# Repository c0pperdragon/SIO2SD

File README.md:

# SIO2SD
An Arduino-based floppy drive emulator for the Atari 8 bit computers.

This small Arduino build emulates an Atari 1050 floppy drive to connect
to an original Atari 8-bit computer. The program is compatible with
most Arduino boards. And for boards based on the Atmega32u4 it also provides
various log messages on the serial monitor to help debugging (mainly for my own use).

For a breadboard setup like my development device, you will need two push buttons,
two 7-digit LEDs and one SDCard socket (with built-in or separate level shifters) and
some wires and resistors. The connectivity is pretty standard and you will find
the details as comments in the source code.

For a more polished product, I have designed a PCB that can fit into a 3D-printed
case that resembles a tiny floppy drive with the SD card acting as a tiny floppy disk.

## Emulated floppies on SDcard
The floppy drive emulator needs an SDcard containing .ats files for each individual floppy disk.
Because there is no elaborated user-interface on the device, the naming and location of the files
need to follow a fixed system: The files are searched for in a directory ATARI/
on the root of the SDcard. Every disk file must be named nn_Anything.ats with two leading digits that correspond to the
numeric display on the device and the mandatory '_' character. Alternatively you can also
have a folder named nn_Anything with individual files inside. Such a folder will be emulated
as an read-only enhanced density floppy containing these files.

Currently only a very basic support for single density (720 sectors)
and enhanced density (1040 sectors) floppies is provided without special functions for any third-party devices.

## User interface
You can switch though the numbered disks 00 to 99 with the two buttons. This is the maximum number of disks 
supported on a single SDcard. When you switch beyond 99, you will see -- on the display, which means the device
now emulates a switched off floppy drive. Selecting a number for which no diskfile exists will simulate 
a device with no floppy inserted (in this case you can create a diskfile with the DOS format functions).

You can also emulate a second floppy drive, which is very usable for example for holding the save disks
for games that support this. To do so, you need to press both buttons to make the small indicator dot appear
on the left LCD block. This means that the number you see in the display is the floppy that is inserted
in drive 2. This floppy can now also be changed with the two buttons. It is even possible to select the same 
floppy in both drives at once (but this is probably of no great use).

## Latest hardware

## 3D-printed case

My brother went to greate lengths, designing a proper case for the floppy emulator. 
In my oppinion, this now looks absolutely phantastic.

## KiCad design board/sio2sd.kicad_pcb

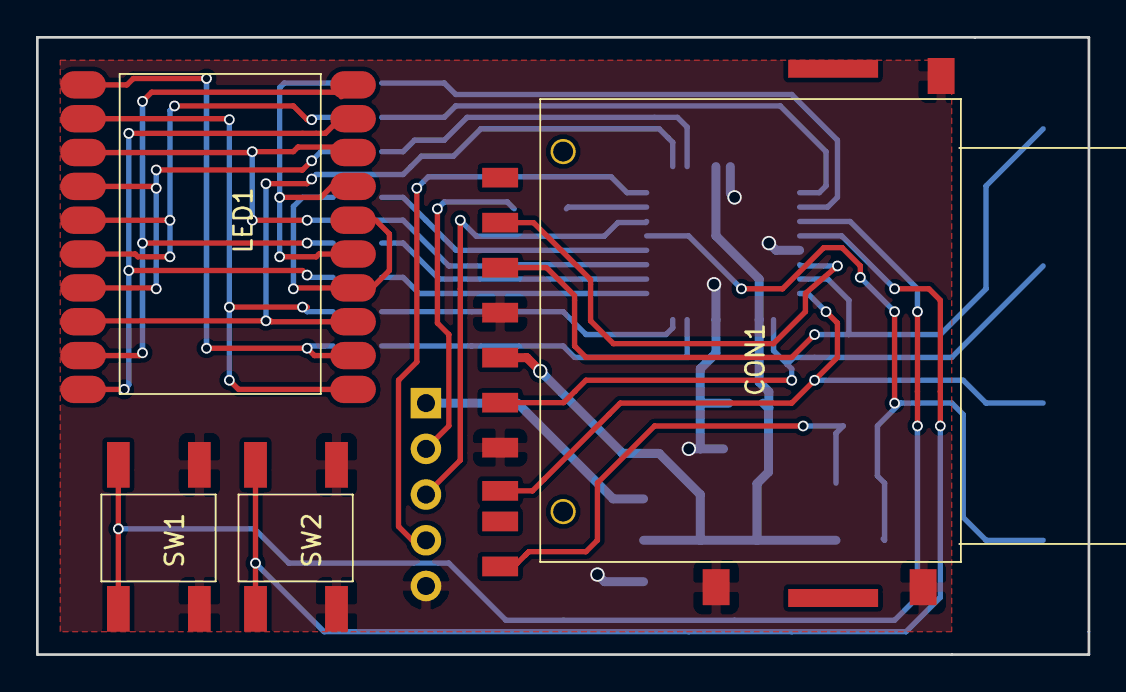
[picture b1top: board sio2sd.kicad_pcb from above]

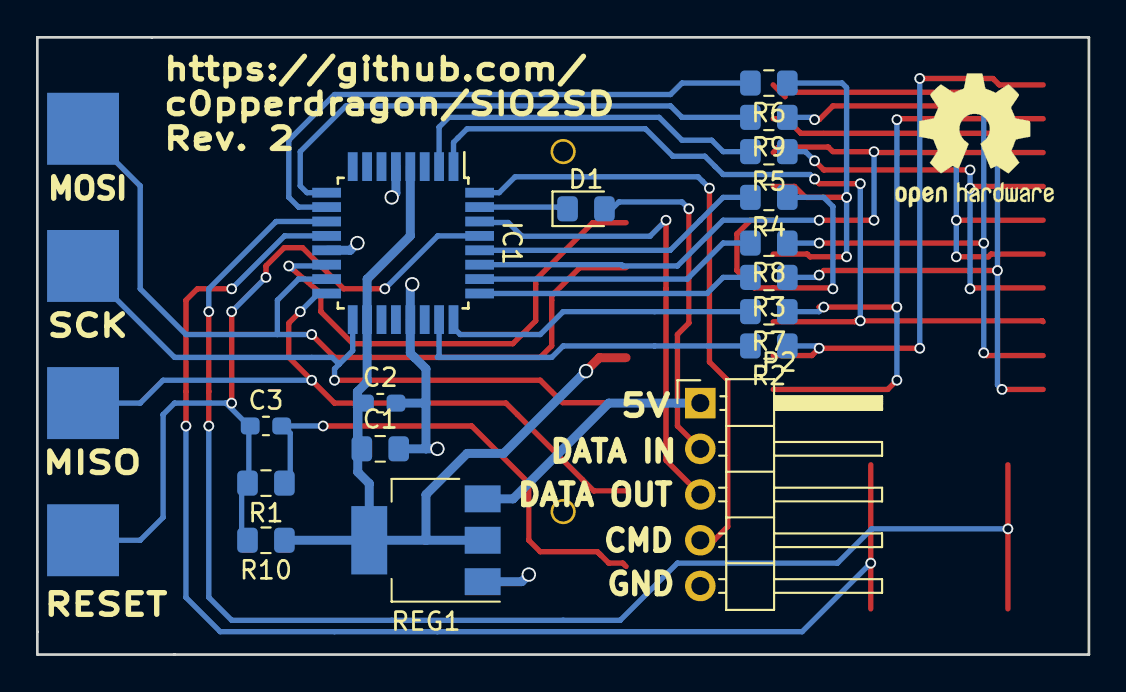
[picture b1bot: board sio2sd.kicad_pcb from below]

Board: 2 copper layers, 58.4 x 34.3 mm, 25 parts (21 on the bottom side), 33 nets.

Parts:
C1: 10uF; C_0805_2012Metric_Pad1.15x1.40mm_HandSolder
C2, C3: 100nF; C_0603_1608Metric_Pad1.05x0.95mm_HandSolder
CON1: SD_Card; sdcardsocket
D1: 0.2V; D_0805_2012Metric_Pad1.15x1.40mm_HandSolder
IC1: ATMEGA328PB-A; TQFP-32_7x7mm_P0.8mm
LED1: LED2DIGIT; led2digit
P2: SIO; PinHeader_1x05_P2.54mm_Horizontal
R1: 220k; R_0805_2012Metric_Pad1.15x1.40mm_HandSolder
R2, R3, R4, R5, R6, R7, R8, R9: 1k; R_0805_2012Metric_Pad1.15x1.40mm_HandSolder
R10: 10k; R_0805_2012Metric_Pad1.15x1.40mm_HandSolder
REG1: LM1117IMPX-3.3; SOT-223
SW1: UP; button
SW2: DOWN; button
W1: MOSI; pad
W2: MISO; pad
W3: SCK; pad
W4: Reset; pad

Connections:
+3V3: C1.1, C2.1, CON1.4, IC1.4, IC1.18, R10.1, REG1.2, REG1.4
+5V: P2.1, REG1.3
/CMD: IC1.32, P2.4
/ChipSelectSD: CON1.1, IC1.14
/Digit0: IC1.27, LED1.8, LED1.13
/Digit1: IC1.1, LED1.3, LED1.18
/MISO: CON1.7, IC1.16, W2.1
/MOSI: CON1.2, IC1.15, W1.1
/RX: IC1.30, P2.3
/Reset: C3.1, IC1.29, R1.2, R10.2, W4.1
/SCK: CON1.5, IC1.17, W3.1
/Seg_4: LED1.14, LED1.17, R5.1
/Seg_5: LED1.15, LED1.16, R9.1
/Seg_6: LED1.5, LED1.7, R6.1
/Seg_A0: LED1.2, LED1.11, R2.1
/Seg_A1: LED1.1, LED1.12, R7.1
/Seg_A2: LED1.9, LED1.20, R3.1
/Seg_A3: LED1.10, LED1.19, R8.1
/Seg_A5: LED1.4, LED1.6, R4.1
/TX: D1.2, P2.2
GND: C1.2, C2.2, CON1.3, CON1.6, CON1.11, CON1.12, CON1.13, IC1.5, IC1.13, IC1.21, P2.5, REG1.1, SW1.2, SW2.2
unnamed: C3.2, CON1.10, R1.1
unnamed: D1.1, IC1.31
unnamed: IC1.2, R5.2
unnamed: IC1.9, R9.2
unnamed: IC1.10, R6.2
unnamed: IC1.11, SW1.1
unnamed: IC1.12, SW2.1
unnamed: IC1.23, R2.2
unnamed: IC1.24, R7.2
unnamed: IC1.25, R3.2
unnamed: IC1.26, R8.2
unnamed: IC1.28, R4.2

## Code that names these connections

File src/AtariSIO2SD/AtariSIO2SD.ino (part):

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// -- connection to Atari SIO port
                              // default arduino RX -> serial data from Atari SIO pin 5
                              // default arduino TX -> serial data to Atari SIO pin 3
#define PIN_SIOCOMMAND  2     //                    -> CMD signal from Atari SIO pin 7

// -- connection to SDCARD
                              // default MOSI
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#define PIN_CHIPSELECT  10    // enables SDCARD on SPI bus

// -- connection to LED display and mode selector
#define PIN_DIGIT0 A4         // enables LED digit 0 (right digit)
#define PIN_DIGIT1 3          // enables LED digit 1 (left digit)
// the digit segments are differently assigned for digit 0 and 1  
//           segment:    a   b   c   d   e   f   g   DP
byte pin_segments0[8] = {A1, A0, A2, 6,  A5, 4,  5,  A3}; 
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    inputlock = false;
  
    // configure and turn of digit selectors 
    pinMode(PIN_DIGIT0, OUTPUT);
    digitalWrite (PIN_DIGIT0, LOW);
    pinMode(PIN_DIGIT1, OUTPUT);
    digitalWrite (PIN_DIGIT1, LOW);  
    // configure and turn off individual digits
    for (i=0; i<8; i++)
    {   pinMode(pin_segments0[i], OUTPUT);
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    if (activedigit==0) 
    {   byte value = selecteddisk[showndiskdrive];
        value = showerror ? 12 : ((value<=99) ? (value % 10) : 10);   // when drive is off: - 
        digitalWrite (PIN_DIGIT1, commoncathode ? HIGH : LOW);  // turn off digit 1
        byte i;
        byte v = digitpatterns[value];
        for (i=0; i<7; i++) 
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        if (activitylight[0]>0) { dot = !dot; }
        if (dot) { digitalWrite (pin_segments0[7], commoncathode ? HIGH : LOW); }
        else     { digitalWrite (pin_segments0[7], commoncathode ? LOW : HIGH); }
        digitalWrite (PIN_DIGIT0, commoncathode ? LOW : HIGH);  // turn on digit 0
    }
    else 
    {   byte value = selecteddisk[showndiskdrive];
        value = showerror ? 11 : ((value<=99) ? (value / 10) : 10);   // when drive is off: -
        digitalWrite (PIN_DIGIT0, commoncathode ? HIGH  : LOW);   // turn off digit 0
        byte i;
        byte v = digitpatterns[value];
        for (i=0; i<7; i++) 
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        if (activitylight[1]>0) { dot = !dot; }
        if (dot) { digitalWrite (pin_segments1[7], commoncathode ? HIGH : LOW); } 
        else     { digitalWrite (pin_segments1[7], commoncathode ? LOW : HIGH); } 
        digitalWrite (PIN_DIGIT1, commoncathode ? LOW : HIGH);  // turn on digit 1
    }  
}

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
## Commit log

2015-08-21 Initial check-in
2015-08-21 extended readme and fixed board layout
2015-08-21 moved code, fixed bugs
2015-09-02 Picture gallery
2016-07-05 archive some rom files
2016-08-21 Prepare more disk files
2016-08-21 Support emulation for multiple floppy drives (D1- D8).
2016-09-06 Mini floppy device
    Board design and adapted arduino sketch (supports large and mini boards)
2016-09-09 changed button assignment for mini1080
2016-09-10 Key repeat for disk change buttons.
2017-03-15 Breadboard version
    Cleaned up the code a bit, removed support for first board design.
2018-03-17 Disk folder reorganization
    To prepare for future changes in the button interface, I have flattened
    and restructured the floppy directory and renamed it to ATARI to match
    the folder name on the SDCARD
2018-03-17 Changed user interface
2018-03-18 Emulate formatting of single and medium density floppies
2018-04-02 Support using directories as disks
2018-04-06 Error state if SDcard not present at startup
2018-04-07 Tweak program to start up fast again
    Instead of initializing SDcard before everything else, defer this until
    actual disk access is done. This is necessary to make the SIO2SD device
    respond immediately to the booting atari.
2018-04-08 Start designing PCB for small SIO2SD variant
2018-04-14 Single board device design
2018-04-15 Change reset circuit, layout fixes
2018-04-15 Small layout fixes, Gerber files
2018-04-16 Docu
2018-04-22 Allow multi-slave configuration
    By inserting a diode into TX -> Data In, the device can emulate an open
    collector to not interfer with other devices on the same bus.
2018-05-05 Remove dependency on external library
2020-08-01 Bring design files to new KiCAD version. Create gerber files.
2020-08-27 3D-printed case, more images.
2020-08-28 formatting
2020-09-02 Small 256 color demo program
2023-06-27 Add the FujuBoink! demo
2023-09-28 Add program: "Atari Control Picture"
